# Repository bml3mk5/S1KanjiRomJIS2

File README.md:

# JIS第二水準内蔵漢字ROMカード for 日立MB-S1

## フォルダ構成

    Board/ ......................... 基板設計
    Documents/ ..................... 説明書など

-----
# JIS Level 2 Kanji Insided Kanji ROM Card for HITACHI MB-S1

## Folders

    Board/ ......................... The circuit board design
    Documents/ ..................... User's Manual etc.

-----
 MailTo: Sasaji (sasaji@s-sasaji.ddo.jp)
 * My Webpage: http://s-sasaji.ddo.jp/bml3mk5/
 * GitHub:     https://github.com/bml3mk5/S1KanjiRomJIS2
 * X(Twitter): https://x.com/bml3mk5

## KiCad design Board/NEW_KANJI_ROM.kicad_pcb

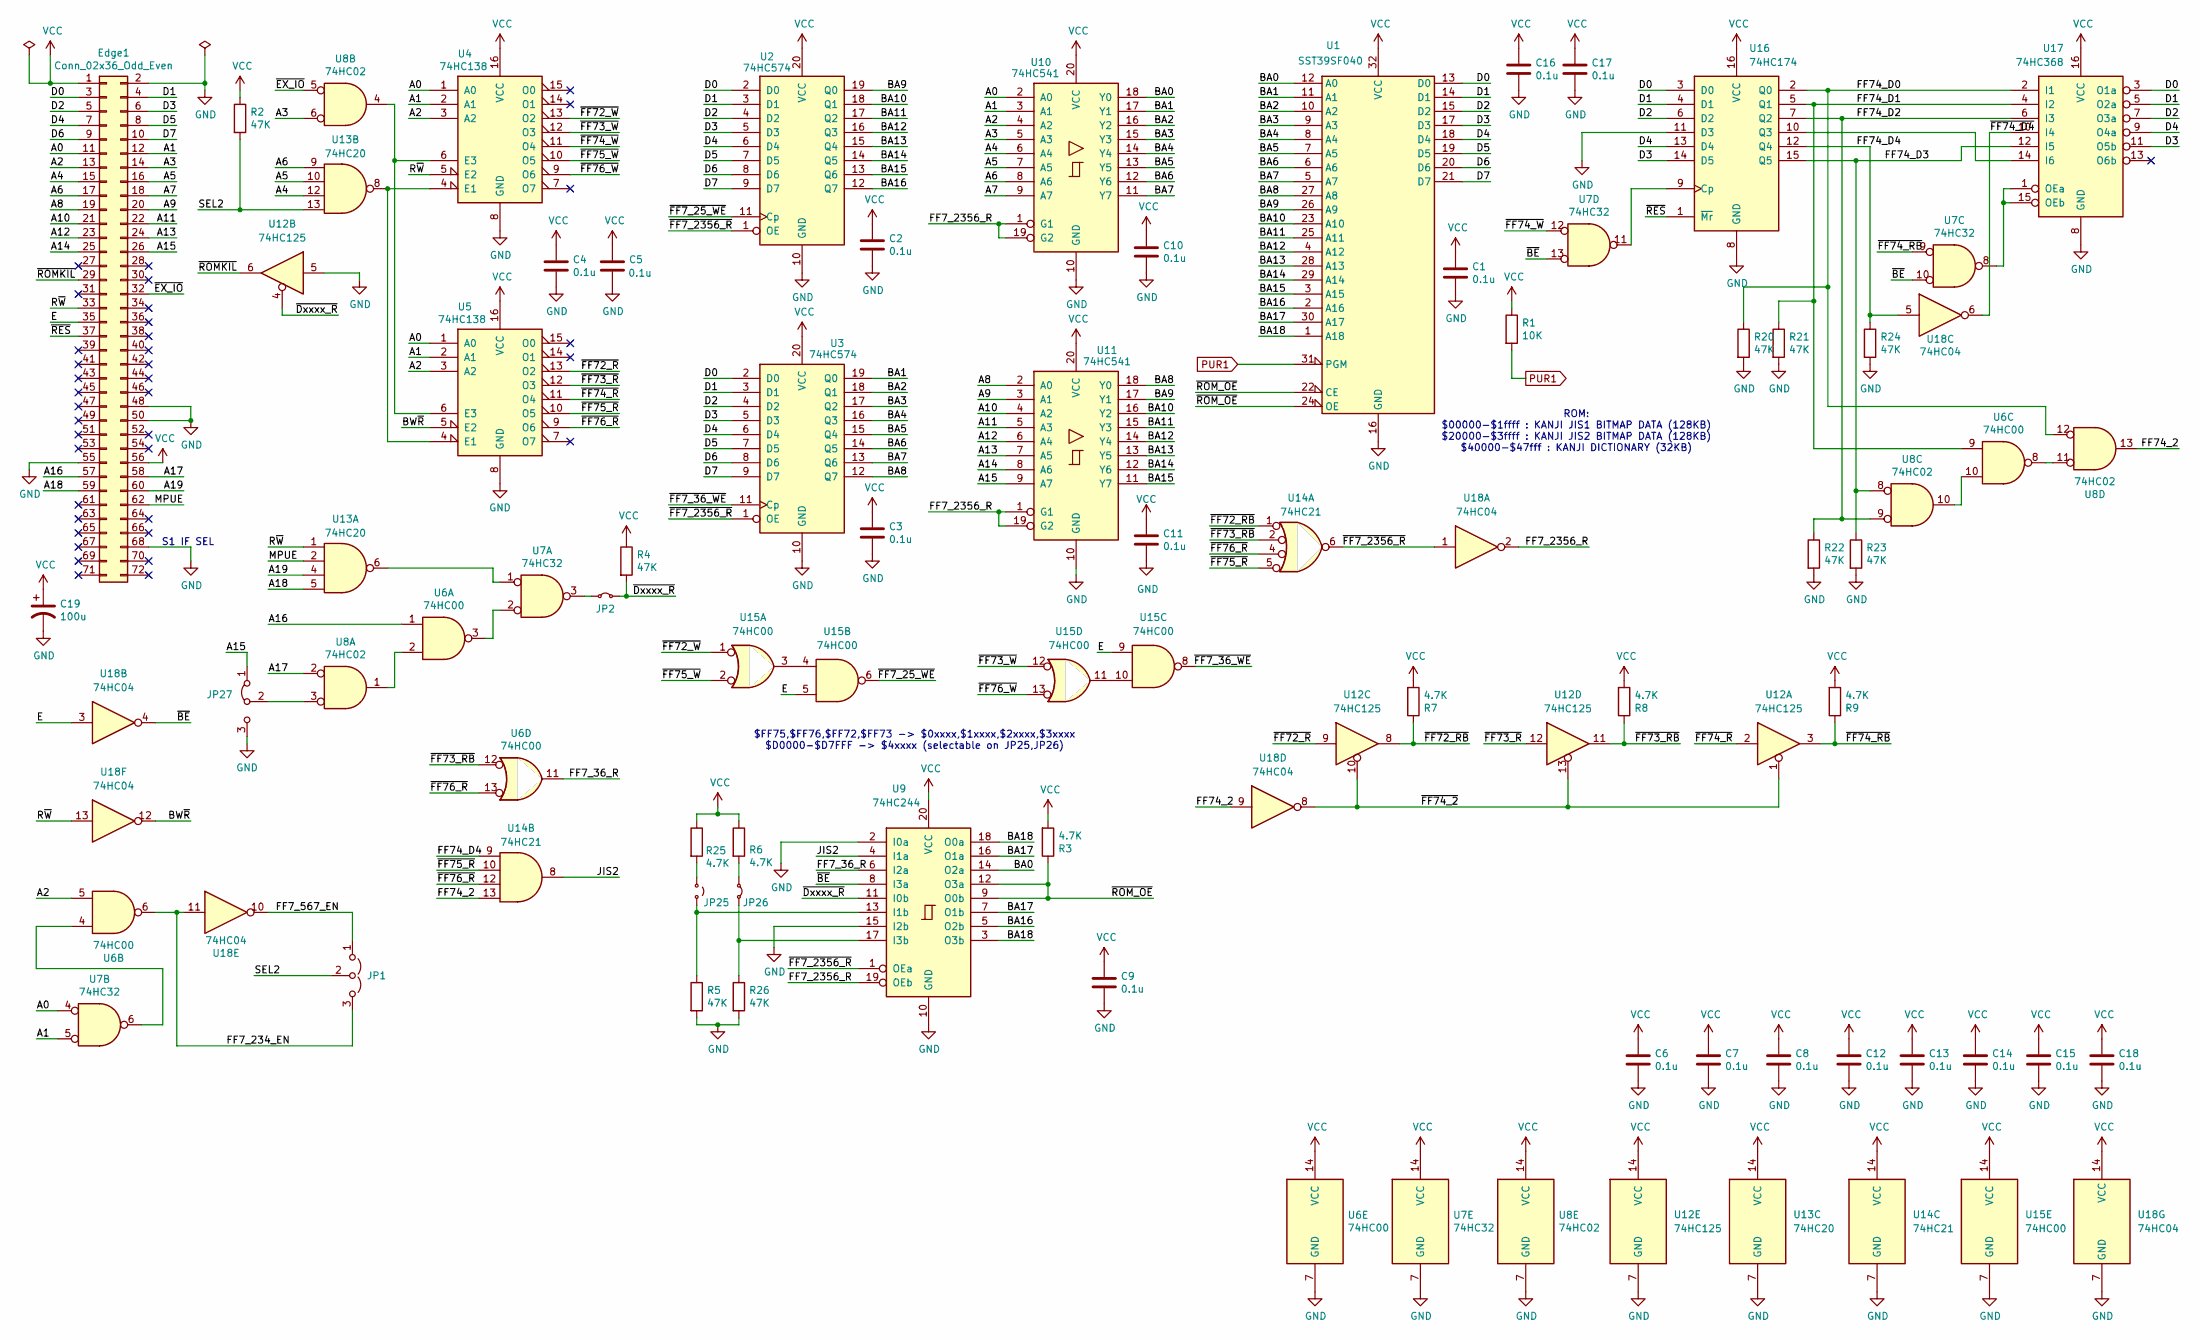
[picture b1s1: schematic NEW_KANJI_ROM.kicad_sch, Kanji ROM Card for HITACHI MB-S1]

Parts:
C1, C2, C3, C4, C5, C6, C7, C8, C9, C10, C11, C12, C13, C14, C15, C16, C17, C18: 0.1u; C_Disc_D3.0mm_W2.0mm_P2.50mm
C19: 100u; CP_Radial_D6.3mm_P2.50mm
Edge1: Conn_02x36_Odd_Even; CardEdge72T
JP1: Jumper_3_Open; PinHeader_1x03_P2.54mm_Vertical
JP2: Jumper_2_Small_Bridged; PinHeader_1x02_P2.54mm_Vertical
JP25: Jumper_2_Small_Open; My_SolderJumper-2_P1mm_Open_SquarePad0.8x1.0mm
JP26: Jumper_2_Small_Bridged; My_SolderJumper-2_P1mm_Bridged_SquarePad0.8x1.0mm
JP27: Jumper_3_Bridged12; My_SolderJumper-3_P1.3mm_Bridged12_RoundedPad1.0x1.5mm
R1: 10K; R_Axial_DIN0204_L3.6mm_D1.6mm_P2.54mm_Vertical
R2, R4, R5, R20, R21, R22, R23, R24, R26: 47K; R_Axial_DIN0204_L3.6mm_D1.6mm_P2.54mm_Vertical
R3, R6, R7, R8, R9, R25: 4.7K; R_Axial_DIN0204_L3.6mm_D1.6mm_P2.54mm_Vertical
U1: SST39SF040; DIP-32_W15.24mm_Socket
U2, U3: 74HC574; DIP-20_W7.62mm_Socket
U4, U5: 74HC138; DIP-16_W7.62mm_Socket
U6, U15: 74HC00; DIP-14_W7.62mm_Socket
U7: 74HC32; DIP-14_W7.62mm_Socket
U8: 74HC02; DIP-14_W7.62mm_Socket
U9: 74HC244; DIP-20_W7.62mm_Socket
U10, U11: 74HC541; DIP-20_W7.62mm_Socket
U12: 74HC125; DIP-14_W7.62mm_Socket
U13: 74HC20; DIP-14_W7.62mm_Socket
U14: 74HC21; DIP-14_W7.62mm_Socket
U16: 74HC174; DIP-16_W7.62mm_Socket
U17: 74HC368; DIP-16_W7.62mm_Socket
U18: 74HC04; DIP-14_W7.62mm_Socket

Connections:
/A0: Edge1.11, U4.1 (A0), U5.1 (A0), U7.4, U10.2 (A0)
/A1: Edge1.12, U4.2 (A1), U5.2 (A1), U7.5, U10.3 (A1)
/A2: Edge1.13, U4.3 (A2), U5.3 (A2), U6.5, U10.4 (A2)
/A3: Edge1.14, U8.6, U10.5 (A3)
/A4: Edge1.15, U10.6 (A4), U13.12
/A5: Edge1.16, U10.7 (A5), U13.10
/A6: Edge1.17, U10.8 (A6), U13.9
/A7: Edge1.18, U10.9 (A7)
/A8: Edge1.19, U11.2 (A0)
/A9: Edge1.20, U11.3 (A1)
/A10: Edge1.21, U11.4 (A2)
/A11: Edge1.22, U11.5 (A3)
/A12: Edge1.23, U11.6 (A4)
/A13: Edge1.24, U11.7 (A5)
/A14: Edge1.25, U11.8 (A6)
/A15: Edge1.26, JP27.1 (A), U11.9 (A7)
/A16: Edge1.57, U6.1
/A17: Edge1.58, U8.2
/A18: Edge1.59, U13.5
/A19: Edge1.60, U13.4
/BA0: U1.12 (A0), U9.14 (O2a), U10.18 (Y0)
/BA1: U1.11 (A1), U3.19 (Q0), U10.17 (Y1)
/BA2: U1.10 (A2), U3.18 (Q1), U10.16 (Y2)
/BA3: U1.9 (A3), U3.17 (Q2), U10.15 (Y3)
/BA4: U1.8 (A4), U3.16 (Q3), U10.14 (Y4)
/BA5: U1.7 (A5), U3.15 (Q4), U10.13 (Y5)
/BA6: U1.6 (A6), U3.14 (Q5), U10.12 (Y6)
/BA7: U1.5 (A7), U3.13 (Q6), U10.11 (Y7)
/BA8: U1.27 (A8), U3.12 (Q7), U11.18 (Y0)
/BA9: U1.26 (A9), U2.19 (Q0), U11.17 (Y1)
/BA10: U1.23 (A10), U2.18 (Q1), U11.16 (Y2)
/BA11: U1.25 (A11), U2.17 (Q2), U11.15 (Y3)
/BA12: U1.4 (A12), U2.16 (Q3), U11.14 (Y4)
/BA13: U1.28 (A13), U2.15 (Q4), U11.13 (Y5)
/BA14: U1.29 (A14), U2.14 (Q5), U11.12 (Y6)
/BA15: U1.3 (A15), U2.13 (Q6), U11.11 (Y7)
/BA16: U1.2 (A16), U2.12 (Q7), U9.5 (O2b)
/BA17: U1.30 (A17), U9.7 (O1b), U9.16 (O1a)
/BA18: U1.1 (A18), U9.3 (O3b), U9.18 (O0a)
/BW~R: U5.5 (E2), U18.12
/D0: Edge1.3, U1.13 (D0), U2.2 (D0), U3.2 (D0), U16.3 (D0), U17.3 (O1a)
/D1: Edge1.4, U1.14 (D1), U2.3 (D1), U3.3 (D1), U16.4 (D1), U17.5 (O2a)
/D2: Edge1.5, U1.15 (D2), U2.4 (D2), U3.4 (D2), U16.6 (D2), U17.7 (O3a)
/D3: Edge1.6, U1.17 (D3), U2.5 (D3), U3.5 (D3), U16.14 (D5), U17.11 (O5b)
/D4: Edge1.7, U1.18 (D4), U2.6 (D4), U3.6 (D4), U16.13 (D4), U17.9 (O4a)
/D5: Edge1.8, U1.19 (D5), U2.7 (D5), U3.7 (D5)
/D6: Edge1.9, U1.20 (D6), U2.8 (D6), U3.8 (D6)
/D7: Edge1.10, U1.21 (D7), U2.9 (D7), U3.9 (D7)
/E: Edge1.35, U15.5, U15.9, U18.3
/FF7_36_R: U6.11, U9.6 (I2a)
/FF7_234_EN: JP1.3 (B), U6.6, U18.11
/FF7_567_EN: JP1.1 (A), U18.10
/FF7_2356_R: U9.19 (OEb), U10.1 (G1), U10.19 (G2), U11.1 (G1), U11.19 (G2), U18.2
/FF74_2: U8.13, U14.13, U18.9
/FF74_D0: R20.1, U8.12, U16.2 (Q0), U17.2 (I1)
/FF74_D1: R21.1, U6.9, U16.5 (Q1), U17.4 (I2)
/FF74_D2: R22.1, U8.9, U16.7 (Q2), U17.6 (I3)
/FF74_D3: R23.1, U8.8, U16.15 (Q5), U17.12 (I5)
/FF74_D4: R24.1, U14.9, U16.12 (Q4), U18.5
/JIS2: U9.4 (I1a), U14.8
/MPUE: Edge1.62, U13.2
/R~W: Edge1.33, U4.5 (E2), U13.1, U18.13
/SEL2: JP1.2 (C), R2.2, U13.13
/~BE: U7.10, U7.13, U9.8 (I3a), U18.4
/~Dxxxx_R: JP2.2 (B), R4.2, U9.11 (I0b), U12.4
/~EX_IO: Edge1.32, U8.5
/~FF7_25_WE: U2.11 (Cp), U15.6
/~FF7_36_WE: U3.11 (Cp), U15.8
/~FF7_2356_R: U2.1 (OE), U3.1 (OE), U9.1 (OEa), U14.6, U18.1
/~FF72_RB: R7.1, U12.8, U14.1
/~FF72_R: U5.13 (O2), U12.9
/~FF72_W: U4.13 (O2), U15.1
/~FF73_RB: R8.1, U6.12, U12.11, U14.2
/~FF73_R: U5.12 (O3), U12.12
/~FF73_W: U4.12 (O3), U15.12
/~FF74_2: U12.1, U12.10, U12.13, U18.8
/~FF74_D4: U17.10 (I4), U18.6
/~FF74_RB: R9.1, U7.9, U12.3
/~FF74_R: U5.11 (O4), U12.2
/~FF74_W: U4.11 (O4), U7.12
/~FF75_R: U5.10 (O5), U14.5, U14.10
/~FF75_W: U4.10 (O5), U15.2
/~FF76_R: U5.9 (O6), U6.13, U14.4, U14.12
/~FF76_W: U4.9 (O6), U15.13
/~RES: Edge1.37, U16.1 (~Mr)
/~ROMKIL: Edge1.29, U12.6
/~ROM_OE: R3.1, U1.22 (CE), U1.24 (OE), U9.9 (O0b), U9.12 (O3a)
GND: C1.2, C2.2, C3.2, C4.2, C5.2, C6.2, C7.2, C8.2, C9.2, C10.2, C11.2, C12.2, C13.2, C14.2, C15.2, C16.2, C17.2, C18.2, C19.2, Edge1.2, Edge1.48, Edge1.50, Edge1.55, Edge1.68, JP27.3 (B), R5.2, R20.2, R21.2, R22.2, R23.2, R24.2, R26.2, U1.16 (GND), U2.10 (GND), U3.10 (GND), U4.8 (GND), U5.8 (GND), U6.7 (GND), U7.7 (GND), U8.7 (GND), U9.2 (I0a), U9.10 (GND), U9.15 (I2b), U10.10 (GND), U11.10 (GND), U12.5, U12.7 (GND), U13.7 (GND), U14.7 (GND), U15.7 (GND), U16.8 (GND), U16.11 (D3), U17.8 (GND), U18.7 (GND)
unnamed: JP2.1 (A), U7.3
unnamed: JP25.1 (A), R25.2
unnamed: JP25.2 (B), R5.1, U9.13 (I1b)
unnamed: JP26.1 (A), R6.2
unnamed: JP26.2 (B), R26.1, U9.17 (I3b)
unnamed: JP27.2 (C), U8.3
unnamed: U4.4 (E1), U5.4 (E1), U13.8
unnamed: U4.6 (E3), U5.6 (E3), U8.4
unnamed: U6.2, U8.1
unnamed: U6.3, U7.2
unnamed: U6.4, U7.6
unnamed: U6.8, U8.11
unnamed: U6.10, U8.10
unnamed: U7.1, U13.6
unnamed: U15.3, U15.4
unnamed: U15.10, U15.11
unnamed: U7.11, U16.9 (Cp)
unnamed: U16.10 (Q3), U17.14 (I6)
unnamed: U7.8, U17.1 (OEa), U17.15 (OEb)
PUR1: R1.2, U1.31 (PGM)
VCC: C1.1, C2.1, C3.1, C4.1, C5.1, C6.1, C7.1, C8.1, C9.1, C10.1, C11.1, C12.1, C13.1, C14.1, C15.1, C16.1, C17.1, C18.1, C19.1, Edge1.1, Edge1.56, R1.1, R2.1, R3.2, R4.1, R6.1, R7.2, R8.2, R9.2, R25.1, U1.32 (VCC), U2.20 (VCC), U3.20 (VCC), U4.16 (VCC), U5.16 (VCC), U6.14 (VCC), U7.14 (VCC), U8.14 (VCC), U9.20 (VCC), U10.20 (VCC), U11.20 (VCC), U12.14 (VCC), U13.14 (VCC), U14.14 (VCC), U15.14 (VCC), U16.16 (VCC), U17.16 (VCC), U18.14 (VCC)

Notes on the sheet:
S1 IF SEL
ROM: $00000-$1ffff : KANJI JIS1 BITMAP DATA (128KB) $20000-$3ffff : KANJI JIS2 BITMAP DATA (128KB) $40000-$47fff : KANJI DICTIONARY (32KB)
$FF75,$FF76,$FF72,$FF73 -> $0xxxx,$1xxxx,$2xxxx,$3xxxx $D0000-$D7FFF -> $4xxxx (selectable on JP25,JP26)

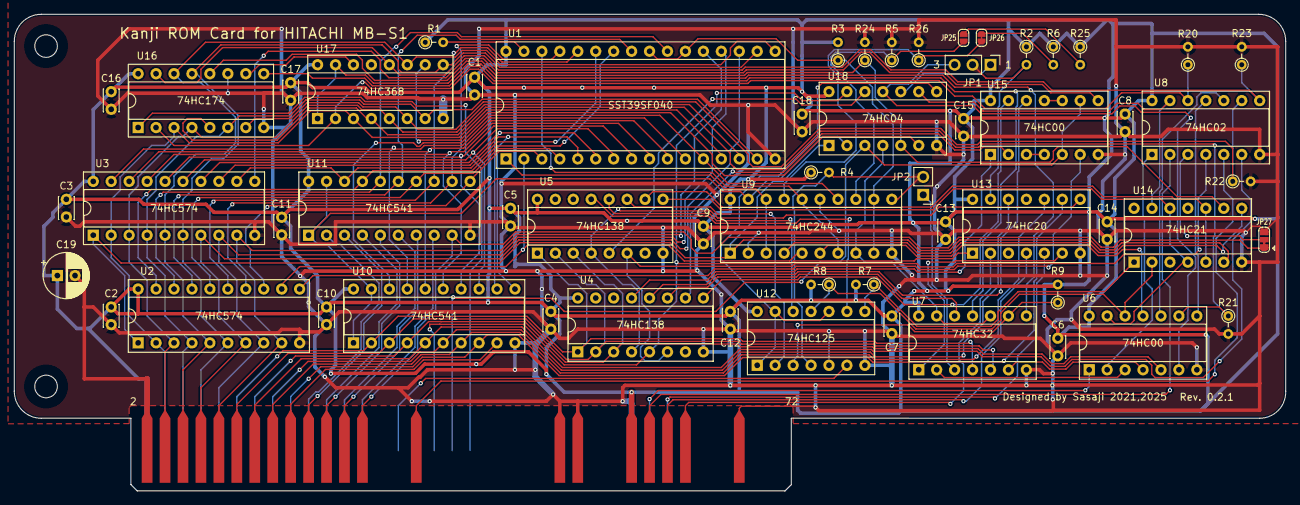
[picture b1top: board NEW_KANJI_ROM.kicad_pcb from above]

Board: 2 copper layers, 180.0 x 67.5 mm, 59 parts (0 on the bottom side), 109 nets.

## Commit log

2026-02-01 Board revision 0.2.1
